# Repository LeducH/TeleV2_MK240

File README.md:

# Logitech adapter

This is project is based on a telev2 project [link][2]

## Parts

23-pin connector [link][1]

[1]:https://www.devicemart.co.kr/goods/view?no=20898
[2]: https://www.youtube.com/watch?v=22MFteWbMIw

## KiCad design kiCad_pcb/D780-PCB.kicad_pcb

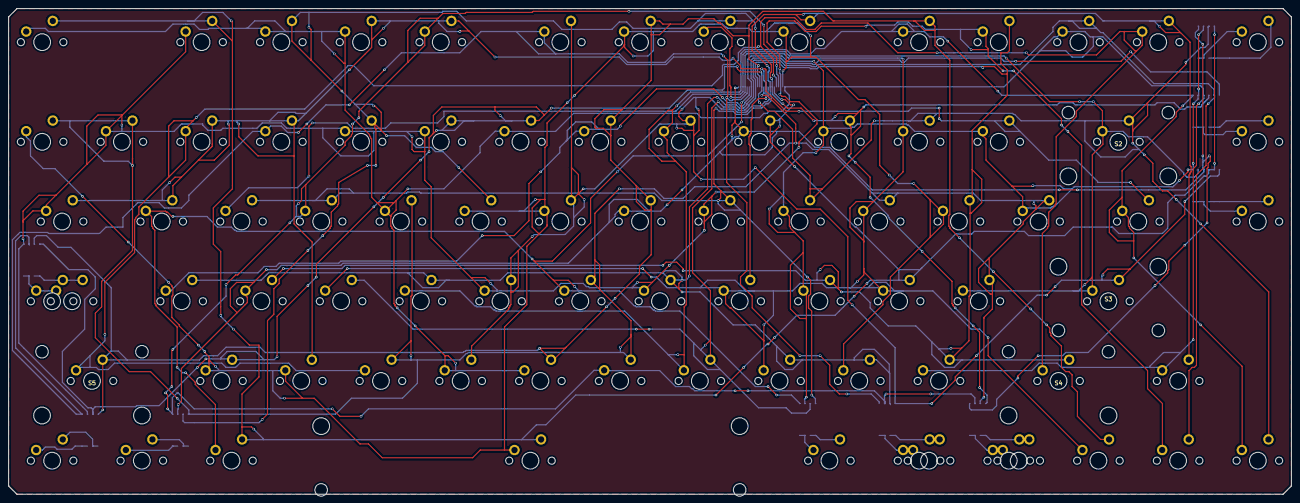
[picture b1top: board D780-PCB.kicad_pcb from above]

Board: 2 copper layers, 306.6 x 116.1 mm, 98 parts (0 on the bottom side), 41 nets.

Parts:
D1, D2, D3, D4, D5, D6, D7: DIP4
D8, D9: DIP6
K1: S; CHERRY_MX
K2: U; CHERRY_MX
K3: PRTSCR; CHERRY_MX
K4, K84: FN; CHERRY_MX
K5: 9; CHERRY_MX
K6: F; CHERRY_MX
K7: M; CHERRY_MX
K8: F9; CHERRY_MX
K9: RIGHT; CHERRY_MX
K10: \; CHERRY_MX
K11: 8; CHERRY_MX
K12: INS; CHERRY_MX
K13: BSPC; CHERRY_MX
K14: ' "; CHERRY_MX
K15: ENTER; CHERRY_MX
K16: W; CHERRY_MX
K17: , <; CHERRY_MX
K18: D; CHERRY_MX
K19: LEFT; CHERRY_MX
K20: -; CHERRY_MX
K21: P; CHERRY_MX
K22: K; CHERRY_MX
K23: F7; CHERRY_MX
K24: ; :; CHERRY_MX
K25, K85: R_CTRL; CHERRY_MX
K26: L_CTRL; CHERRY_MX
K27: 3; CHERRY_MX
K28: F5; CHERRY_MX
K29: R_ALT; CHERRY_MX
K30: H; CHERRY_MX
K31: Q; CHERRY_MX
K32: L_ALT; CHERRY_MX
K33: A; CHERRY_MX
K34: L; CHERRY_MX
K35: 7; CHERRY_MX
K36: O; CHERRY_MX
K37: ]; CHERRY_MX
K38: + =; CHERRY_MX
K40: 0; CHERRY_MX
K41: DEL; CHERRY_MX
K42: R_SHIFT; CHERRY_MX
K43: L_SHIFT; CHERRY_MX
K44: C; CHERRY_MX
K45: 2; CHERRY_MX
K46: F12; CHERRY_MX
K47: N; CHERRY_MX
K48: F4; CHERRY_MX
K50: E; CHERRY_MX
K51: WIN; CHERRY_MX
K52: J; CHERRY_MX
K53: DOWN; CHERRY_MX
K54: F10; CHERRY_MX
K55, K83: CAPS; CHERRY_MX
K56: 5; CHERRY_MX
K57: 1; CHERRY_MX
K58: TAB; CHERRY_MX
K59: G; CHERRY_MX
K60: I; CHERRY_MX
K61: 4; CHERRY_MX
K62: F1; CHERRY_MX
K63: . >; CHERRY_MX
K64: [; CHERRY_MX
K65: F6; CHERRY_MX
K66: Z; CHERRY_MX
K67: ` ~~; CHERRY_MX
K68: X; CHERRY_MX
K69: Y; CHERRY_MX
K70: F8; CHERRY_MX
K71: T; CHERRY_MX
K72: SPACE; CHERRY_MX
K73: F11; CHERRY_MX
K74: / ?; CHERRY_MX
K75: B; CHERRY_MX
K76: 6; CHERRY_MX
K77: R; CHERRY_MX
K78: F3; CHERRY_MX
K79: V; CHERRY_MX
K80: UP; CHERRY_MX
K81: F2; CHERRY_MX
K82: ESC; CHERRY_MX
S1: STAB_LONG; STAB_LONG_V1
S2, S3, S4, S5: STAB_SHORT
U1: CONN; CONNECTOR_23PIN

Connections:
unnamed: D1.1, D3.2, D4.1, K27.1, K28.1, U1.5
unnamed: D1.2, D6.2, D7.1, K47.1, K48.1, K50.1, U1.20
unnamed: D1.3, D8.6, K6.2, K17.2, K33.2, K52.2, K63.2, U1.8
unnamed: D1.4, D9.6, K11.2, K15.2, K28.2, K59.2, K69.2, K79.2, U1.15
unnamed: D1.5, D1.6, K25.1, K85.1
unnamed: D1.7, D1.8, K25.2, K85.2
unnamed: D2.1, K30.1, K31.1, K32.1, U1.6
unnamed: D2.2, D5.2, D8.2, D9.1, K33.1, K34.1, K35.1, K36.1, K37.1, K38.1, K40.1, U1.7
unnamed: D2.3, D8.5, K7.2, K18.2, K53.2, K73.2, U1.9
unnamed: D2.4, K16.2, K46.2, K50.2, K60.2, K70.2, K80.2, U1.16
unnamed: D2.5, D2.6, K29.1
unnamed: D2.7, D2.8, K29.2
unnamed: D3.1, D4.2, K52.1, K53.1, K54.1, K56.1, K57.1, K58.1, K59.1, K60.1, K61.1, K62.1, U1.21
unnamed: D3.3, D4.4, K2.2, K8.2, K19.2, K35.2, K43.2, K65.2, K75.2, U1.11
unnamed: D3.4, D4.3, D5.3, K9.2, K13.2, K20.2, K36.2, K56.2, K66.2, K76.2, U1.12
unnamed: D3.5, D3.6, K55.1, K83.1
unnamed: D3.7, D3.8, K55.2, K83.2
unnamed: D4.5, D4.6, K26.1
unnamed: D4.7, D4.8, K26.2
unnamed: D5.1, D6.1, D7.2, D9.3, K1.1, K2.1, K5.1, U1.1
unnamed: D5.4, D9.4, D9.5, K5.2, K24.2, K32.2, K62.2, K72.2, K82.2, U1.18
unnamed: D5.5, D5.6, K3.1
unnamed: D5.7, D5.8, K3.2
unnamed: D6.3, D7.4, K14.2, K21.2, K30.2, K37.2, K44.2, K47.2, K57.2, K67.2, K77.2, U1.13
unnamed: D6.4, D7.3, D8.4, K23.2, K40.2, K61.2, K71.2, K81.2, U1.17
unnamed: D6.5, D6.6, K4.1, K84.1
unnamed: D6.7, D6.8, K4.2, K84.2
unnamed: D7.5, D7.6, K51.1
unnamed: D7.7, D7.8, K51.2
unnamed: D8.1, K6.1, K7.1, K8.1, K9.1, K10.1, K11.1, U1.2
unnamed: D8.3, K73.1, K74.1, K75.1, K76.1, K77.1, K78.1, K79.1, K80.1, K81.1, K82.1, U1.23
unnamed: D8.7, D8.8, D8.9, K12.1
unnamed: D8.10, D8.11, D8.12, K12.2
unnamed: D9.2, K13.1, K14.1, K15.1, K16.1, U1.3
unnamed: D9.7, D9.8, D9.9, K41.1
unnamed: D9.10, D9.11, D9.12, K41.2
unnamed: K1.2, K34.2, K42.2, K54.2, K64.2, K74.2, U1.10
unnamed: K10.2, K22.2, K27.2, K31.2, K38.2, K45.2, K48.2, K58.2, K68.2, K78.2, U1.14
unnamed: K17.1, K18.1, K19.1, K20.1, K21.1, K22.1, K23.1, K24.1, U1.4
unnamed: K42.1, K43.1, K44.1, K45.1, K46.1, U1.19
unnamed: K63.1, K64.1, K65.1, K66.1, K67.1, K68.1, K69.1, K70.1, K71.1, K72.1, U1.22

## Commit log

2022-08-08 readme update
